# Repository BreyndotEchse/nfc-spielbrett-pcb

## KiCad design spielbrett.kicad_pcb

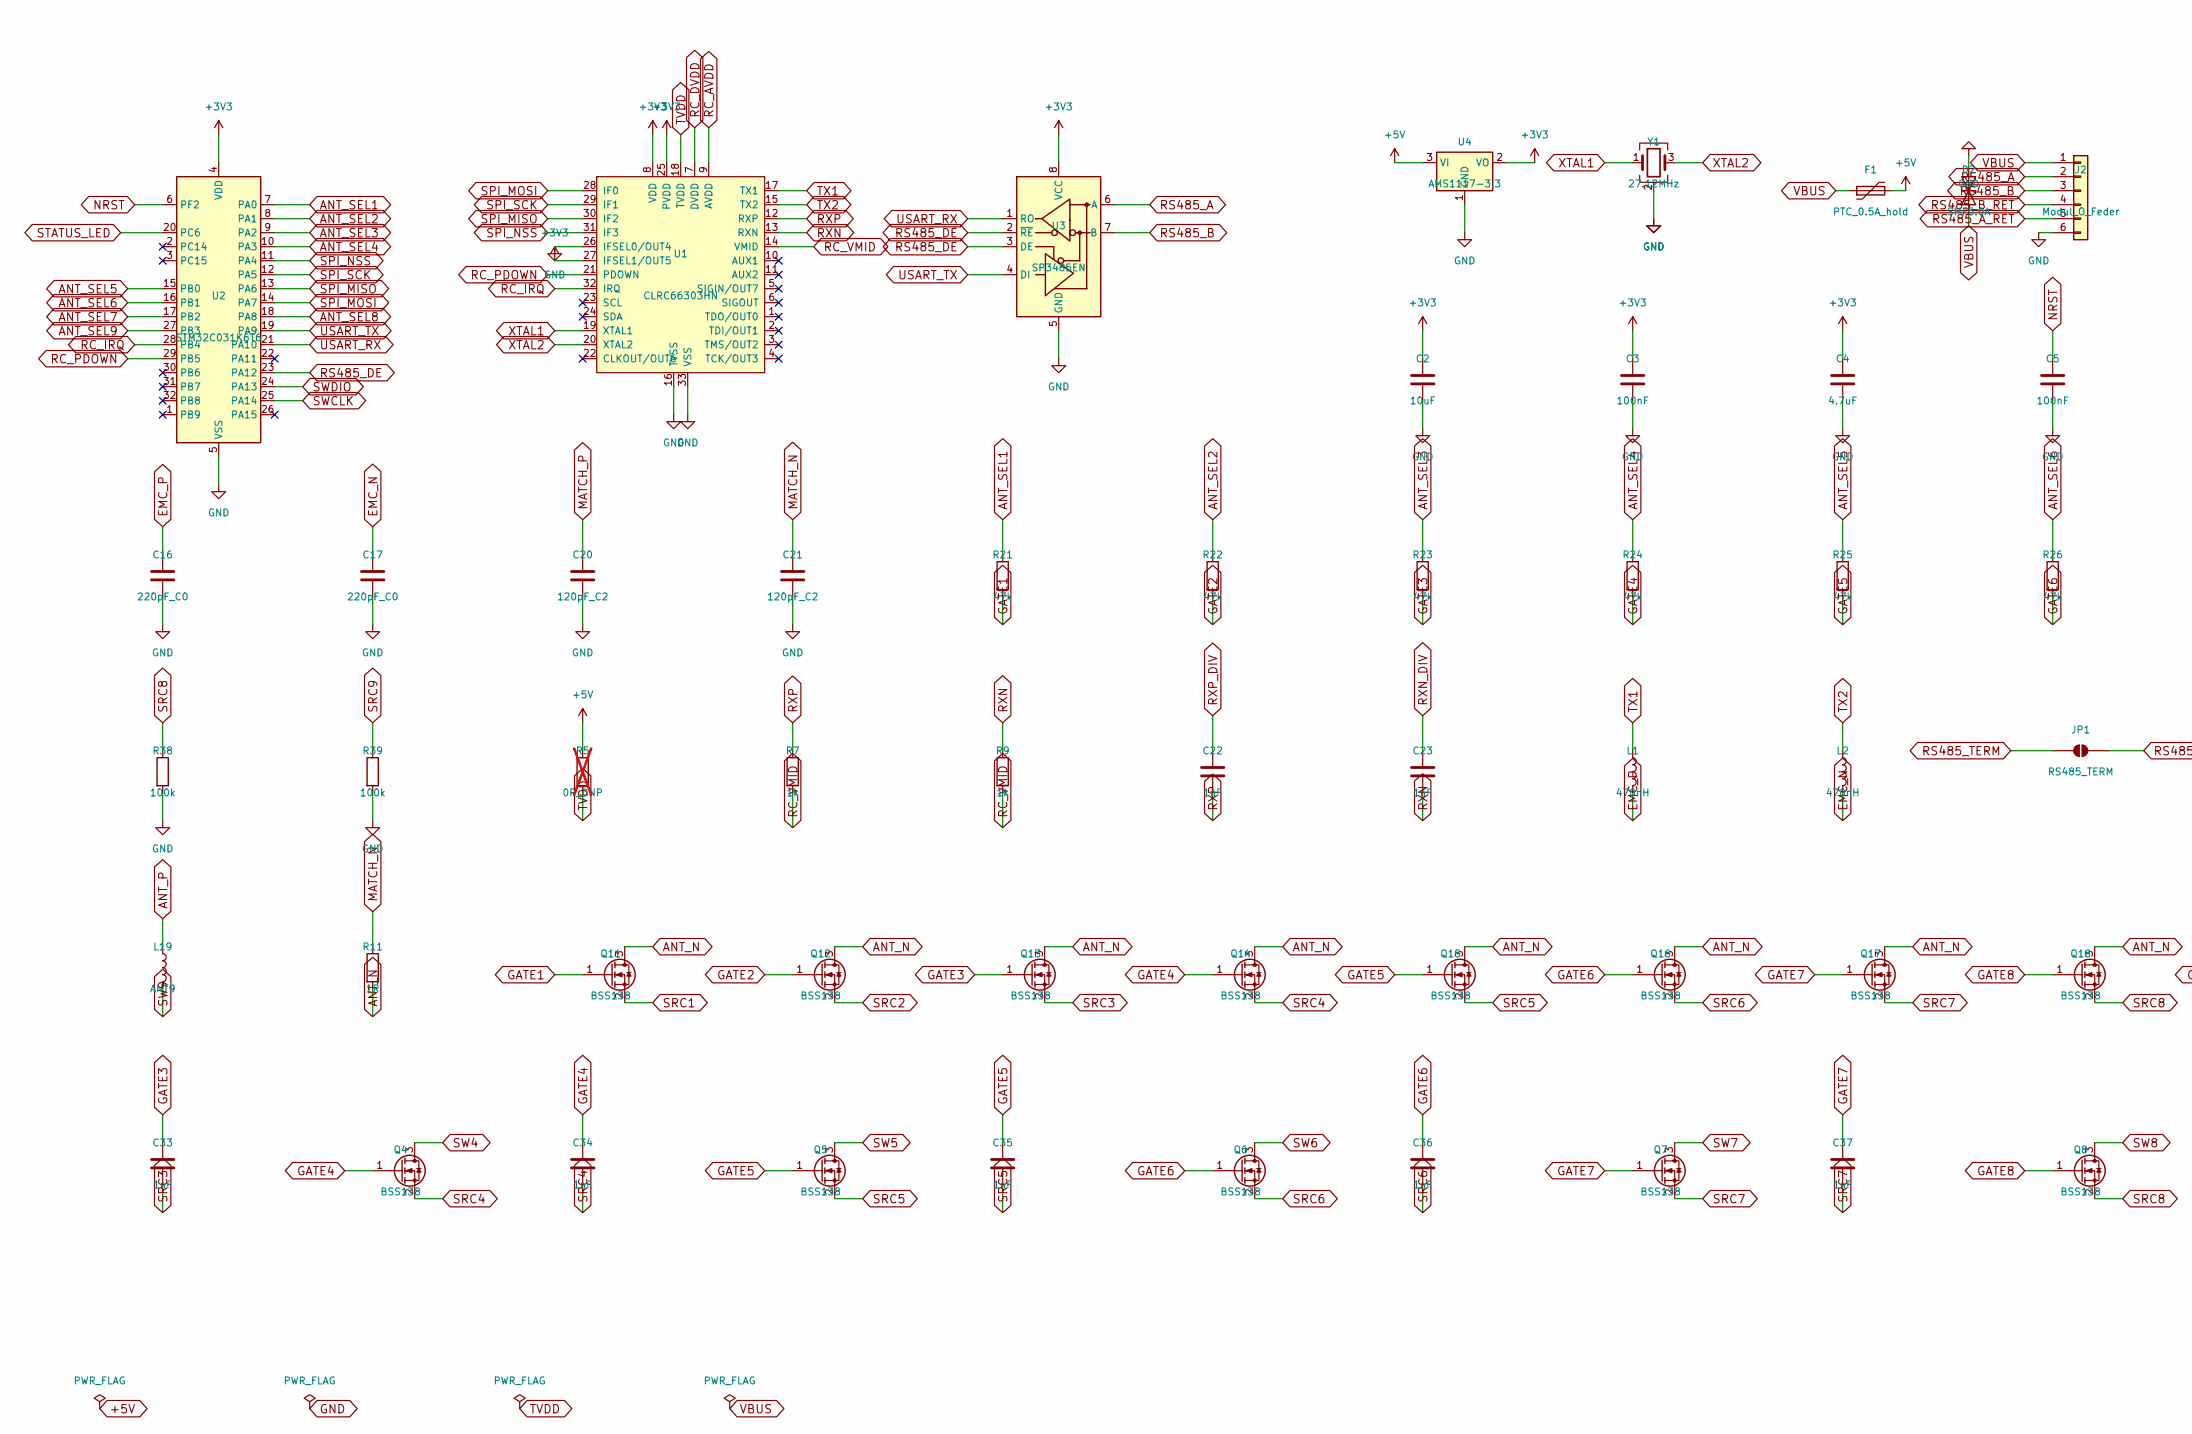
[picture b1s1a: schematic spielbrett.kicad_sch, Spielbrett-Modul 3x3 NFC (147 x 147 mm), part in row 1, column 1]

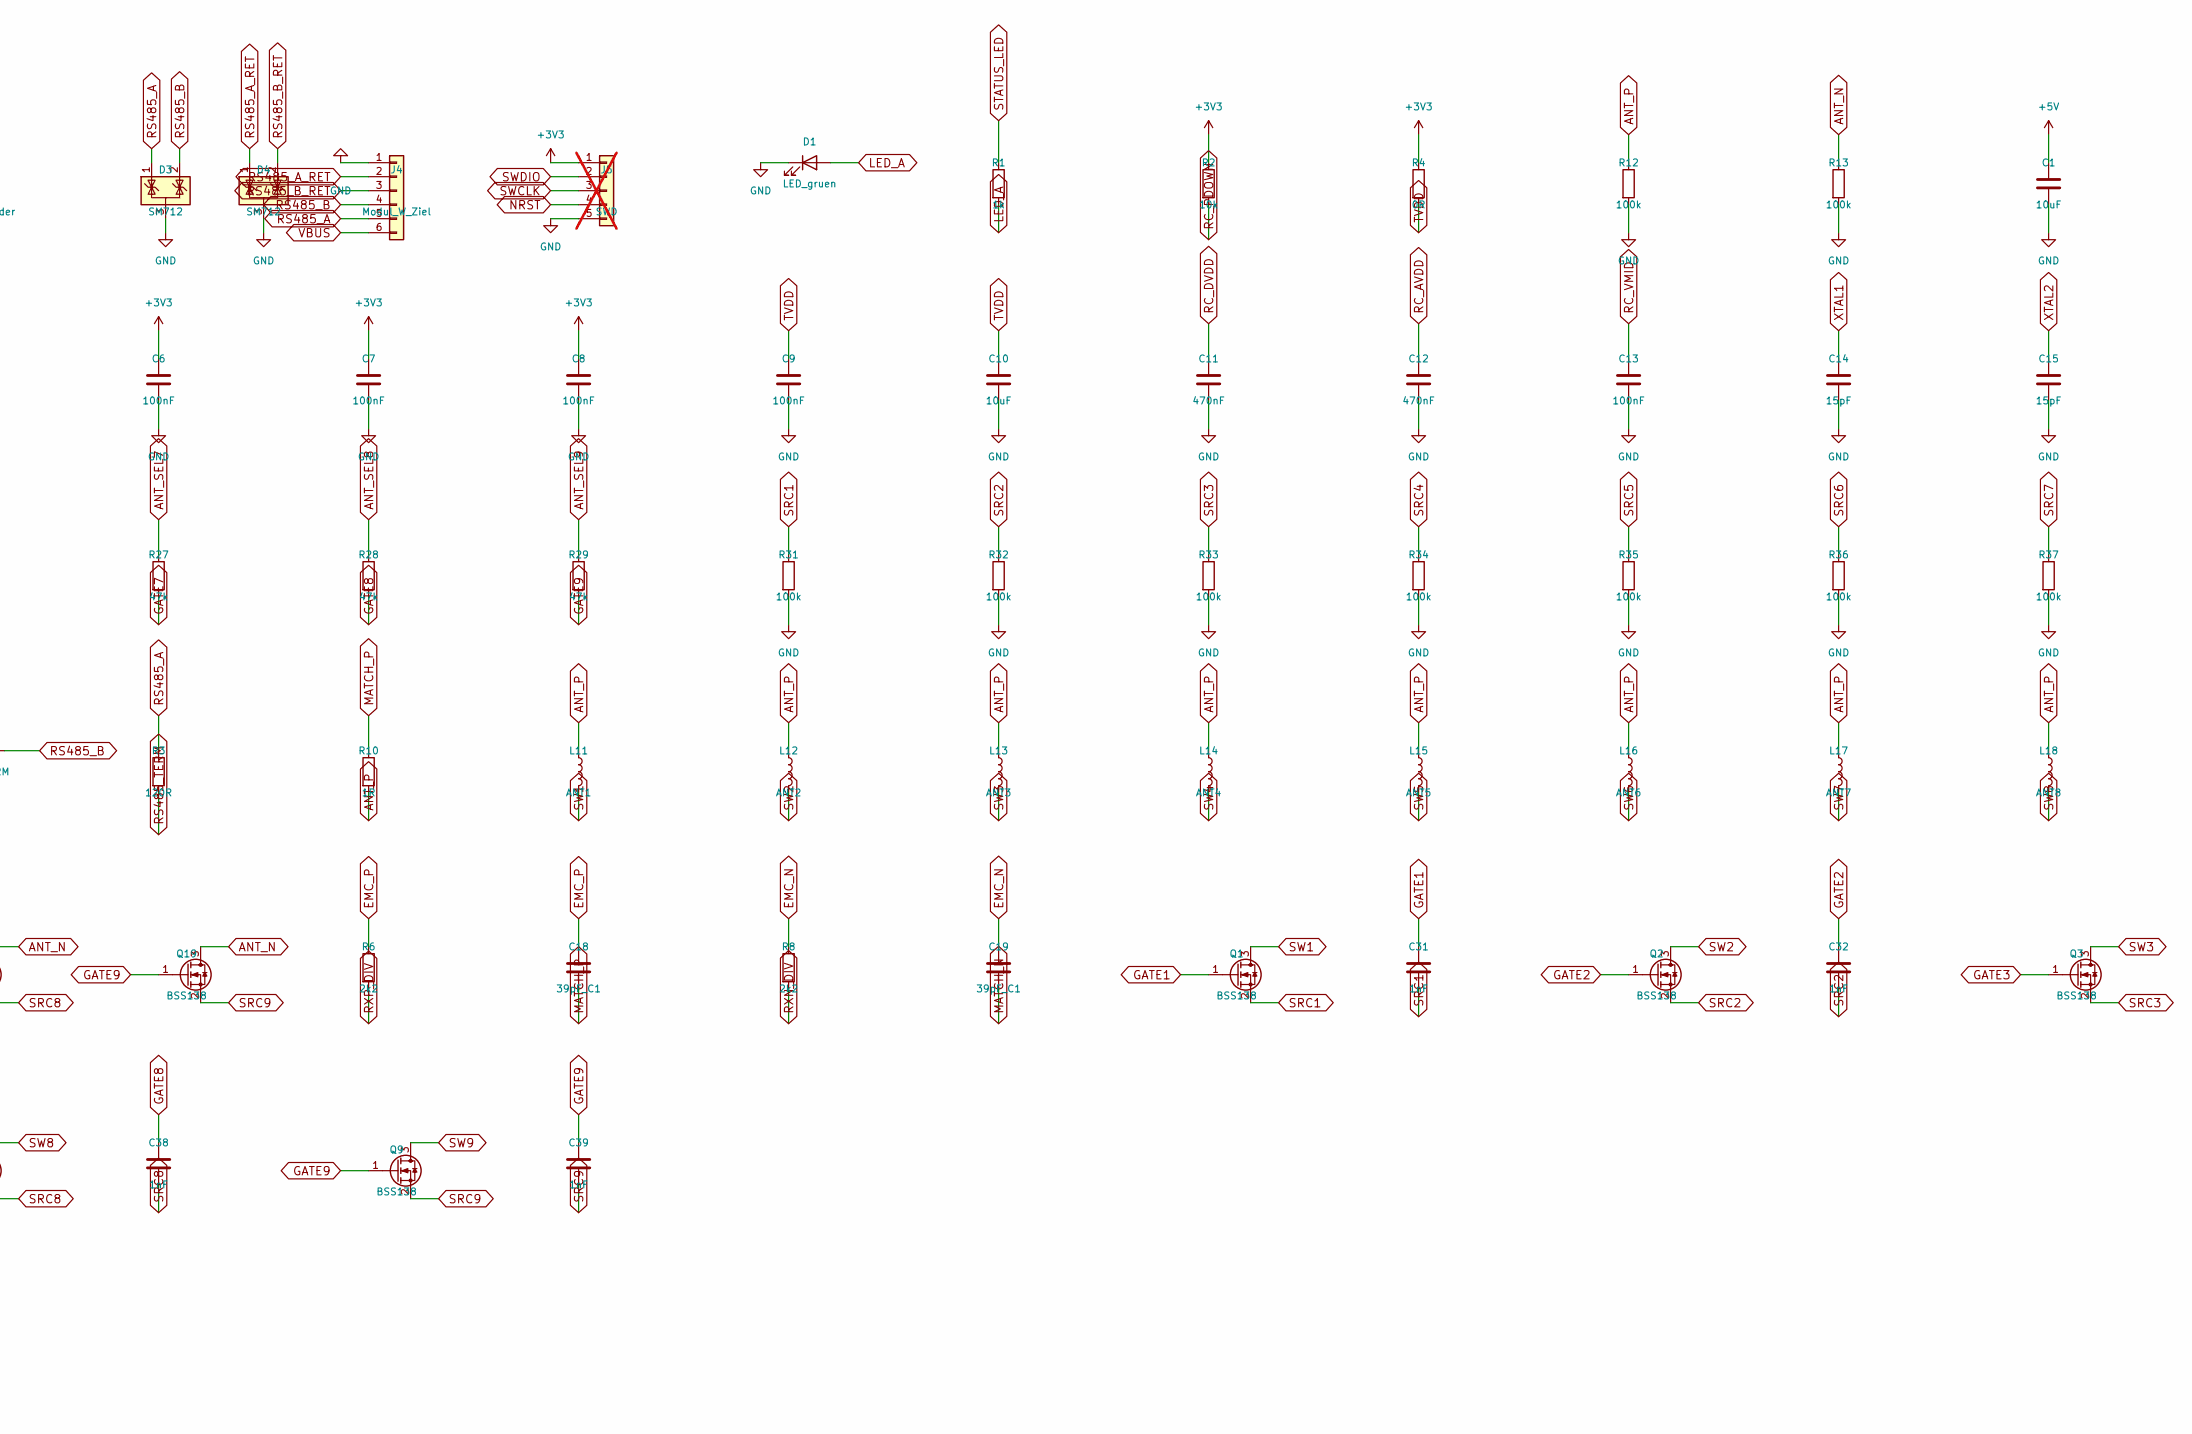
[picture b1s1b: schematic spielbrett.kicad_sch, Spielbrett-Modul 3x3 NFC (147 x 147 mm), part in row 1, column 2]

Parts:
C1, C2, C10: 10uF; C_0805_2012Metric; LCSC C15850
C3, C5, C6, C7, C8, C9, C13: 100nF; C_0603_1608Metric; LCSC C14663
C4: 4.7uF; C_0603_1608Metric; LCSC C19666
C11, C12: 470nF; C_0603_1608Metric; LCSC C1623
C14, C15: 15pF; C_0603_1608Metric; LCSC C1644
C16, C17: 220pF_C0; C_0603_1608Metric; LCSC C106210
C18, C19: 39pF_C1; C_0603_1608Metric; LCSC C107049
C20, C21: 120pF_C2; C_0603_1608Metric; LCSC C107035
C22, C23, C31, C32, C33, C34, C35, C36, C37, C38, C39: 1nF; C_0603_1608Metric; LCSC C1588
D1: LED_gruen; LED_0603_1608Metric; LCSC C12624
D2: SMF5.0A; D_SOD-123F; LCSC C19077497
D3, D4: SM712; SOT-23; LCSC C521963
F1: PTC_0.5A_hold; Fuse_1206_3216Metric; LCSC C7542947
J2: Modul_O_Feder; HC-CX-PH254-1x6PW-4050B-E; MPN HC-CX-PH254-1x6PW-4050B-E; LCSC C56314391
J4: Modul_W_Ziel; HC-CX-FH254-1x6PW-4040B-E; MPN HC-CX-FH254-1x6PW-4040B-E; LCSC C56314419
J5: SWD; PinHeader_1x05_P1.27mm_Vertical; not fitted
JP1: RS485_TERM; SolderJumper-2_P1.3mm_Open_RoundedPad1.0x1.5mm
L1, L2: 470nH; L_0805_2012Metric; LCSC C412002
L11: ANT1; NFC_Coil_D24_N5_W0.4_S0.4
L12: ANT2; NFC_Coil_D24_N5_W0.4_S0.4
L13: ANT3; NFC_Coil_D24_N5_W0.4_S0.4
L14: ANT4; NFC_Coil_D24_N5_W0.4_S0.4
L15: ANT5; NFC_Coil_D24_N5_W0.4_S0.4
L16: ANT6; NFC_Coil_D24_N5_W0.4_S0.4
L17: ANT7; NFC_Coil_D24_N5_W0.4_S0.4
L18: ANT8; NFC_Coil_D24_N5_W0.4_S0.4
L19: ANT9; NFC_Coil_D24_N5_W0.4_S0.4
Q1, Q2, Q3, Q4, Q5, Q6, Q7, Q8, Q9, Q11, Q12, Q13, Q14, Q15, Q16, Q17, Q18, Q19: BSS138; SOT-23; LCSC C7420339
R1, R7, R9: 1k; R_0603_1608Metric; LCSC C21190
R2: 10k; R_0603_1608Metric; LCSC C25804
R3: 120R; R_0603_1608Metric; LCSC C22787
R4: 0R; R_0805_2012Metric; LCSC C17477
R5: 0R_DNP; R_0805_2012Metric; LCSC C17477; not fitted
R6, R8: 2k2; R_0603_1608Metric; LCSC C4190
R10, R11: 1R; R_0603_1608Metric; LCSC C22936
R12, R13, R31, R32, R33, R34, R35, R36, R37, R38, R39: 100k; R_0603_1608Metric; LCSC C25803
R21, R22, R23, R24, R25, R26, R27, R28, R29: 47k; R_0603_1608Metric; LCSC C25819
U1: CLRC66303HN; HVQFN-32-1EP_5x5mm_P0.5mm_EP3.1x3.1mm; MPN CLRC66303HNY; LCSC C2988350
U2: STM32C031K6T6; LQFP-32_7x7mm_P0.8mm; MPN STM32C031K6T6; LCSC C5456169
U3: SP3485EN; SOIC-8_3.9x4.9mm_P1.27mm; MPN SP3485EN-L/TR; LCSC C8963
U4: AMS1117-3.3; SOT-223-3_TabPin2; LCSC C6186
Y1: 27.12MHz; Crystal_SMD_3225-4Pin_3.2x2.5mm; LCSC C29975

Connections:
+3V3: C2.1, C3.1, C4.1, C6.1, C7.1, C8.1, J5.1, R2.1, R4.1, U1.8 (VDD), U1.25 (PVDD), U1.27 (IFSEL1/OUT5), U2.4 (VDD), U3.8 (VCC), U4.2 (VO)
+5V: C1.1, F1.2, R5.1, U4.3 (VI)
ANT_N: Q11.3 (D), Q12.3 (D), Q13.3 (D), Q14.3 (D), Q15.3 (D), Q16.3 (D), Q17.3 (D), Q18.3 (D), Q19.3 (D), R11.2, R13.1
ANT_P: L11.1, L12.1, L13.1, L14.1, L15.1, L16.1, L17.1, L18.1, L19.1, R10.2, R12.1
ANT_SEL1: R21.1, U2.7 (PA0)
ANT_SEL2: R22.1, U2.8 (PA1)
ANT_SEL3: R23.1, U2.9 (PA2)
ANT_SEL4: R24.1, U2.10 (PA3)
ANT_SEL5: R25.1, U2.15 (PB0)
ANT_SEL6: R26.1, U2.16 (PB1)
ANT_SEL7: R27.1, U2.17 (PB2)
ANT_SEL8: R28.1, U2.18 (PA8)
ANT_SEL9: R29.1, U2.27 (PB3)
EMC_N: C17.1, C19.1, L2.2, R8.1
EMC_P: C16.1, C18.1, L1.2, R6.1
GATE1: C31.1, Q1.1 (G), Q11.1 (G), R21.2
GATE2: C32.1, Q2.1 (G), Q12.1 (G), R22.2
GATE3: C33.1, Q3.1 (G), Q13.1 (G), R23.2
GATE4: C34.1, Q4.1 (G), Q14.1 (G), R24.2
GATE5: C35.1, Q5.1 (G), Q15.1 (G), R25.2
GATE6: C36.1, Q6.1 (G), Q16.1 (G), R26.2
GATE7: C37.1, Q7.1 (G), Q17.1 (G), R27.2
GATE8: C38.1, Q8.1 (G), Q18.1 (G), R28.2
GATE9: C39.1, Q9.1 (G), Q19.1 (G), R29.2
GND: C1.2, C2.2, C3.2, C4.2, C5.2, C6.2, C7.2, C8.2, C9.2, C10.2, C11.2, C12.2, C13.2, C14.2, C15.2, C16.2, C17.2, C20.2, C21.2, D1.1 (K), D2.2 (A2), D3.3 (A), D4.3 (A), J2.6, J4.1, J5.5, R12.2, R13.2, R31.2, R32.2, R33.2, R34.2, R35.2, R36.2, R37.2, R38.2, R39.2, U1.16 (TVSS), U1.26 (IFSEL0/OUT4), U1.33 (VSS), U2.5 (VSS), U3.5 (GND), U4.1 (GND), Y1.2 (G), Y1.4 (G)
LED_A: D1.2 (A), R1.2
MATCH_N: C19.2, C21.1, R11.1
MATCH_P: C18.2, C20.1, R10.1
NRST: C5.1, J5.4, U2.6 (PF2)
RC_AVDD: C12.1, U1.9 (AVDD)
RC_DVDD: C11.1, U1.7 (DVDD)
RC_IRQ: U1.32 (IRQ), U2.28 (PB4)
RC_PDOWN: R2.2, U1.21 (PDOWN), U2.29 (PB5)
RC_VMID: C13.1, R7.2, R9.2, U1.14 (VMID)
RS485_A: D3.1 (K), J2.2, J4.5, R3.1, U3.6 (A)
RS485_A_RET: D4.1 (K), J2.5, J4.2
RS485_B: D3.2 (K), J2.3, J4.4, JP1.2 (B), U3.7 (B)
RS485_B_RET: D4.2 (K), J2.4, J4.3
RS485_DE: U2.23 (PA12), U3.2 (~RE), U3.3 (DE)
RS485_TERM: JP1.1 (A), R3.2
RXN: C23.2, R9.1, U1.13 (RXN)
RXN_DIV: C23.1, R8.2
RXP: C22.2, R7.1, U1.12 (RXP)
RXP_DIV: C22.1, R6.2
SPI_MISO: U1.30 (IF2), U2.13 (PA6)
SPI_MOSI: U1.28 (IF0), U2.14 (PA7)
SPI_NSS: U1.31 (IF3), U2.11 (PA4)
SPI_SCK: U1.29 (IF1), U2.12 (PA5)
SRC1: C31.2, Q1.2 (S), Q11.2 (S), R31.1
SRC2: C32.2, Q2.2 (S), Q12.2 (S), R32.1
SRC3: C33.2, Q3.2 (S), Q13.2 (S), R33.1
SRC4: C34.2, Q4.2 (S), Q14.2 (S), R34.1
SRC5: C35.2, Q5.2 (S), Q15.2 (S), R35.1
SRC6: C36.2, Q6.2 (S), Q16.2 (S), R36.1
SRC7: C37.2, Q7.2 (S), Q17.2 (S), R37.1
SRC8: C38.2, Q8.2 (S), Q18.2 (S), R38.1
SRC9: C39.2, Q9.2 (S), Q19.2 (S), R39.1
STATUS_LED: R1.1, U2.20 (PC6)
SW1: L11.2, Q1.3 (D)
SW2: L12.2, Q2.3 (D)
SW3: L13.2, Q3.3 (D)
SW4: L14.2, Q4.3 (D)
SW5: L15.2, Q5.3 (D)
SW6: L16.2, Q6.3 (D)
SW7: L17.2, Q7.3 (D)
SW8: L18.2, Q8.3 (D)
SW9: L19.2, Q9.3 (D)
SWCLK: J5.3, U2.25 (PA14)
SWDIO: J5.2, U2.24 (PA13)
TX1: L1.1, U1.17 (TX1)
TX2: L2.1, U1.15 (TX2)
USART_RX: U2.21 (PA10), U3.1 (RO)
USART_TX: U2.19 (PA9), U3.4 (DI)
XTAL1: C14.1, U1.19 (XTAL1), Y1.1
XTAL2: C15.1, U1.20 (XTAL2), Y1.3

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
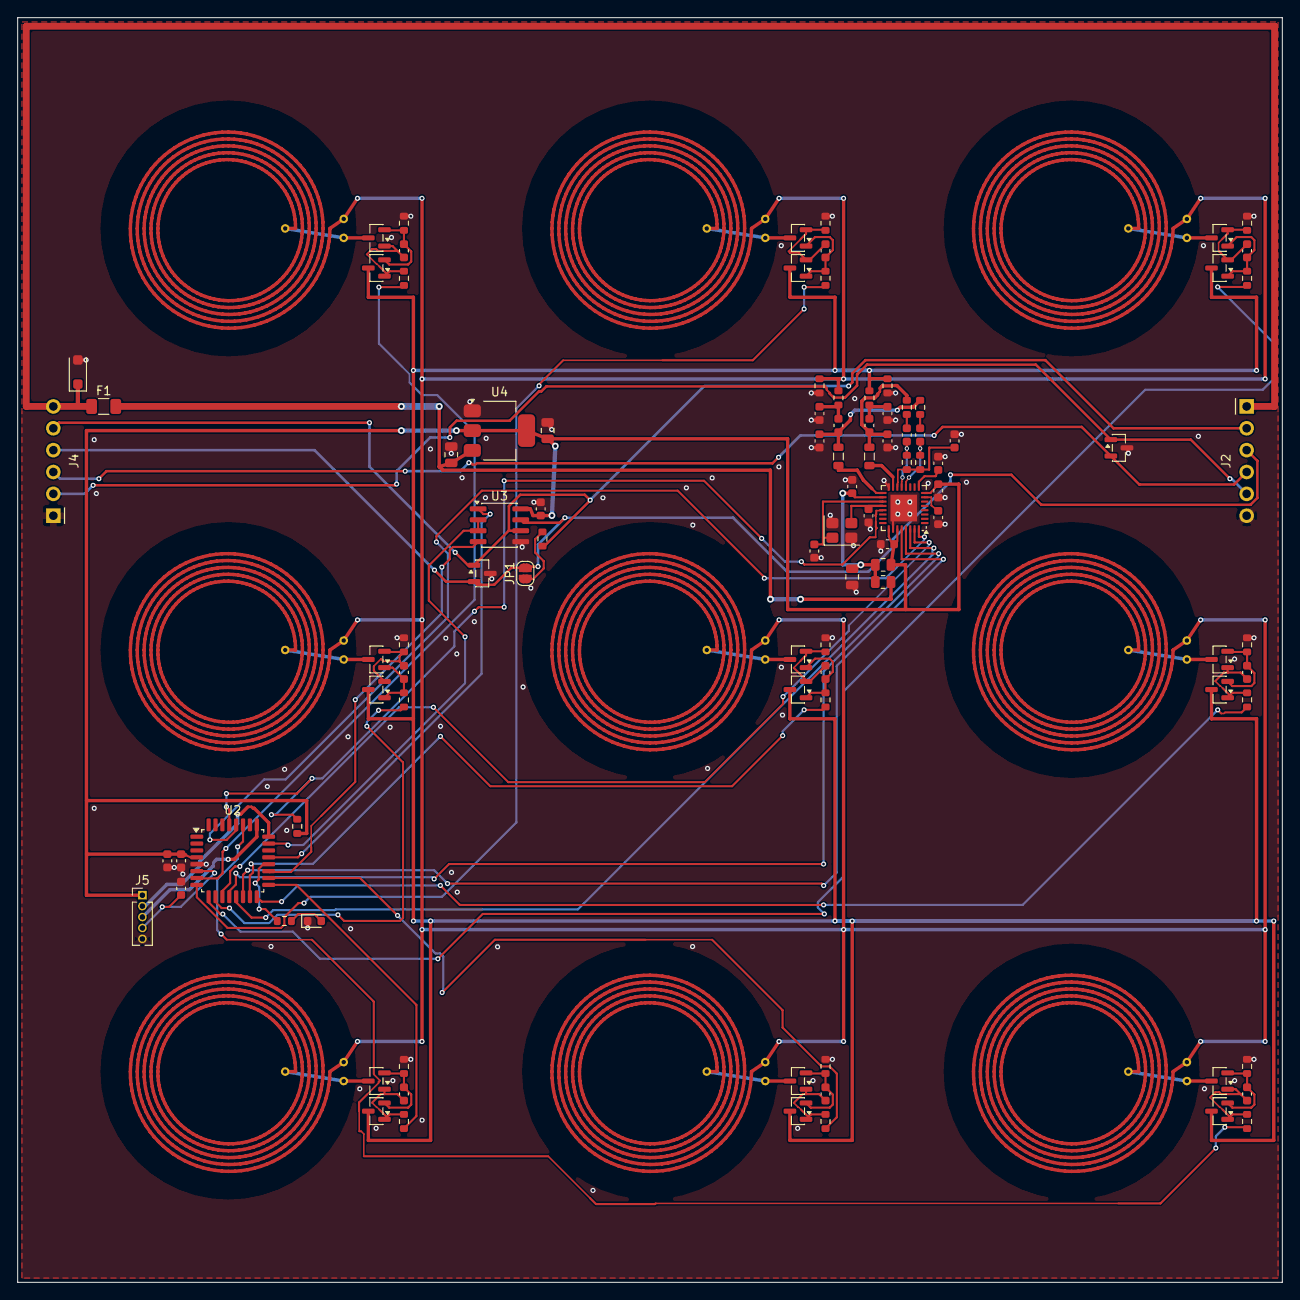
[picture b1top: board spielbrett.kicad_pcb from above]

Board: 2 copper layers, 147.0 x 147.0 mm, 106 parts (0 on the bottom side), 77 nets.

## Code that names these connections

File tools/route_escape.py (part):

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
Alles landet gesperrt in der Gruppe "Escape_Routing"; ein erneuter Lauf ersetzt nur diese Gruppe.

RX     RXN (Pin 13) / RXP (Pin 12) per Via unter den VMID-Pads von R9/R7 hindurch auf B.Cu zum
       Knoten R.1/C.2 (eine Kreuzung VMID <-> RX ist bei dieser Pinfolge topologisch unvermeidbar).
VMID   Pin 14 -> R9.2 -> R7.2 -> rechts hoch -> C13.
AVDD   Pin 9 -> C12.1, DVDD Pin 7 -> C11.1.
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    t([p14, (xv, 84.0), (xv, r9v[1]), r9v], "RC_VMID", w=FINE)
    t([r9v, r7v, (xr, r7v[1]), (xr, c13v[1]), c13v], "RC_VMID", w=SIG)

    # ---------- RXN: Pin 13 -> Via -> B.Cu -> Via zwischen C23.2 und R9.1 ----------
    p13, r9n, c23n = P("U1", 13), P("R9", 1), P("C23", 2)
    vn = (p13[0] + 0.1, 83.45)
    vn2 = (r9n[0], (r9n[1] + c23n[1]) / 2)
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    r.via(vn2, "RXN", SMALL_VIA)
    t([r9n, vn2, c23n], "RXN", w=SIG)

    # ---------- RXP: Pin 12 -> Via -> B.Cu -> Via zwischen C22.2 und R7.1 ----------
    p12, r7p, c22p = P("U1", 12), P("R7", 1), P("C22", 2)
    vp = (p12[0] + 0.35, 83.45)
    vp2 = (r7p[0], (r7p[1] + c22p[1]) / 2)
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    t([p26, (p26[0], ep[1] + 1.2)], "GND", w=SIG)

    # ---------- SPI/IRQ: gestaffelte Ausfaecherung nach rechts unten ----------
    for i, (pin, net) in enumerate([(32, "RC_IRQ"), (31, "SPI_NSS"), (30, "SPI_MISO"),
                                    (29, "SPI_SCK"), (28, "SPI_MOSI")]):
        p = P("U1", pin)
        y = 90.35 + 0.65 * i
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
